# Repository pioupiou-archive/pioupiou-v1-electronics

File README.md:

# pioupiou-v1-electronics

This repository contains the electronic parts of the Pioupiou V1 wind sensor.

## DEPRECATION NOTICE
**THIS REPOSITORY IS NO LONGER ACTIVE.**

**PLEASE MOVE TO THE NEW PROJECT: https://github.com/windbird-sensor/windbird-electronics**

## License

Copyright (c) 2015 Bac Plus Zéro SAS

Copyright (c) 2016 Altostratus SA

Copyright (c) 2021 OpenWindMap SCIC SA and contributors

**Permission is granted to anyone to use this Material for any purpose, including commercial applications, and to alter it and redistribute it freely, subject to the following restrictions:**

**ATTRIBUTION:** You must give appropriate credit, provide a link to the license, and indicate if changes were made. You may do so in any reasonable manner, but not in any way that suggests the licensor endorses you or your use.

**SHARE-ALIKE:** If you remix, transform, or build upon the Material, you must distribute your contributions under the same license as the original. You must include a copy of this License with every copy of this Material or modified version of this Material You distribute or otherwise make available.

**OBLIGATION TO SHARE WITHIN THE OPENWINDMAP NETWORK:** If you use this Material or a modified version of this Material to build a product that collects environmental data, this data must be published within the OpenWindMap network. You must not intentionally degrade the quality of the data, reduce the accuracy of its geolocation or delay its dissemination.

**OPEN-DATA:** If you use this Material or a modified version of this Material to build a product that collects environmental data, this data should be published under an Open-Data license. The chosen license must allow free reuse and redistribution, including from commercial entities and for commercial use. The choosen license must either be compliant with the [Open Definition](https://opendefinition.org/od/2.1/en/) or receive approval from OpenWindMap's board. You are allowed to offer a version of this data under any other license of your choice (including non-free licenses), as long as you also provide an identical version of this data under an Open-Data license as defined in this paragraph.

**DISCLAIMER OF WARRANTY/LIMITATION OF REMEDIES:** OpenWindMap and its contributors have no obligation to support this Material. OpenWindMap and its contributors are providing this Material "AS IS", with no express or implied warranties of any kind, including, but not limited to, any implied warranties of merchantability or fitness for any particular purpose or warranties against infringement of any proprietary rights of a third party.

**OpenWindMap and its contributors will not be liable for any consequential, incidental, or special damages, or any other relief, or for any claim by any third party, arising from your use of this Material.**

For the avoidance of doubt, OpenWindMap may offer this Material under separate terms or conditions or stop distributing this Material at any time; however, doing so will not terminate this License.

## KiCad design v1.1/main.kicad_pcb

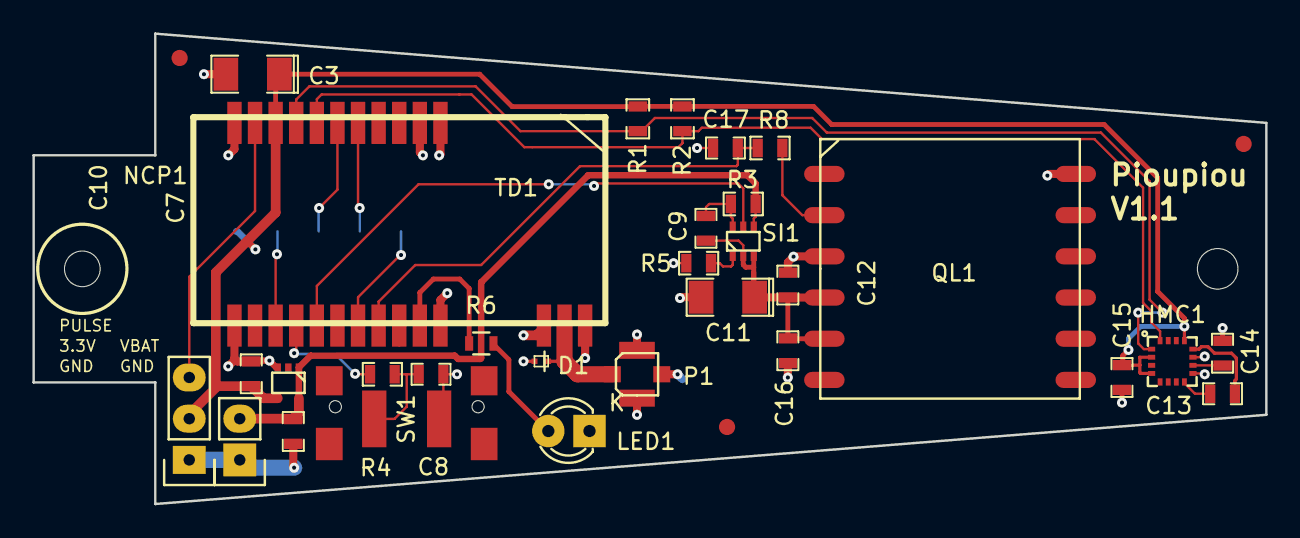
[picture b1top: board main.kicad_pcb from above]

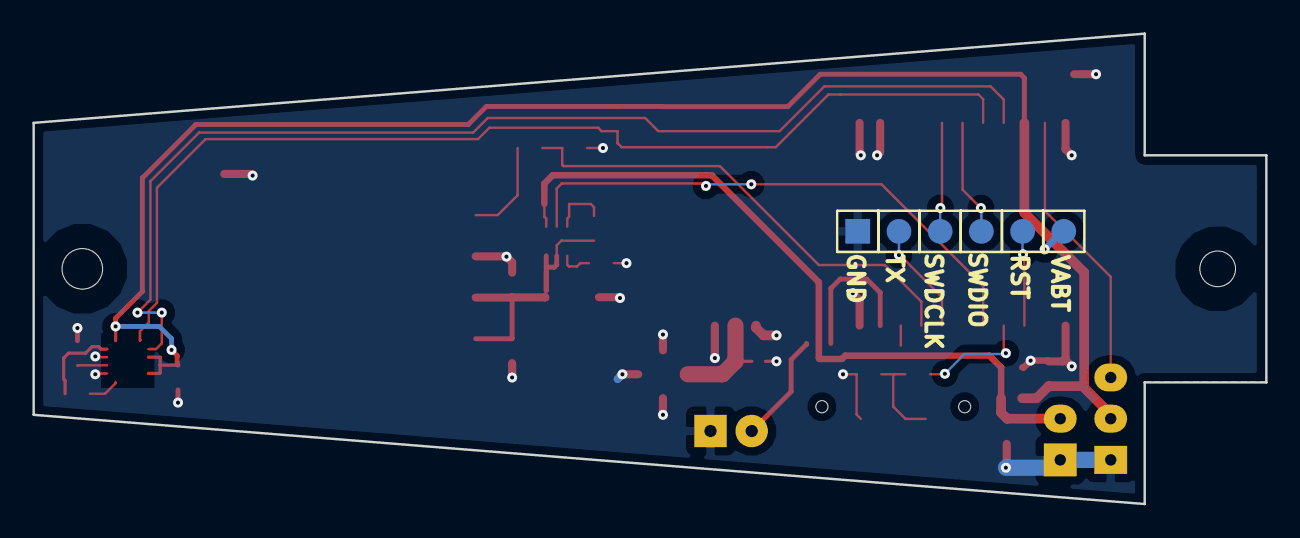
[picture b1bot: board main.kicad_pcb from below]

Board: 2 copper layers, 76.0 x 29.0 mm, 39 parts (6 on the bottom side), 23 nets.

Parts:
BT1: AAA; VIS_BATTERIE
C3: 10uF/6V3; SM1206POL
C7, C10, C12, C16: 100n; SM0603_Capa
C8: 10nF; SM0603_Capa
C9, C17: vide; SM0603_Capa
C11: 10u; SM1206POL
C13: 220nF; SM0603_Capa
C14: 4.7uF; SM0603_Capa
C15: 100nF; SM0603_Capa
D1: ESD9R3.3ST5G; sod923
HMC1: HMC5883L
K1: CONN_3; Socket_Strip_Straight_1x03
LED1: LED-3MM
MIRE-1MM, MIRE-1MM#2, MIRE-1MM#3: VAL**; MIRE-1MM
NCP1: NCP4681
P1: CONN_2; UFL
P3, P4, P5, P6, P7, P8: CONN_1; PIN_ARRAY_1
QL1: L80; PA6H
R1, R2, R4: 10k; SM0603_Resistor
R3: 1M; SM0603_Resistor
R5: 0R; SM0603_Resistor
R6: R_0603
R8: 10K; SM0603_Resistor
SI1: SI1865DL; si1865dl
SW1: SW_PUSH; 1571300
TD1: TD1208

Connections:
/GPSBCKP: C16.1, QL1.5, TD1.17
/GPSVIO: SI1.5, TD1.16
/PULSE_SW: K1.3, TD1.10
/RF: D1.1, P1.1, TD1.24
/RST: P6.1, TD1.14
/RX: C17.1, R8.2, TD1.19
/SCL: HMC1.1, R1.2, TD1.8
/SDA: HMC1.16, R2.2, TD1.7
/SWDCLK: P5.1, TD1.5
/SWDIO: P4.1, TD1.6
/TX: P8.1, TD1.18
/USR_SW: R4.1, TD1.15
/V33: C3.1, C10.1, C15.1, HMC1.2, HMC1.4, HMC1.13, K1.2, NCP1.4, P3.1, R1.1, R2.1, TD1.9
/VBAT: C7.1, NCP1.1, NCP1.5, R3.1, SI1.4
GND: C3.2, C7.2, C8.2, C10.2, C11.2, C12.2, C14.2, C15.2, C16.2, C17.2, D1.2, HMC1.9, HMC1.11, K1.1, LED1.1, NCP1.3, P1.2, P7.1, QL1.3, QL1.12, R5.2, SW1.2, TD1.1, TD1.2, TD1.11, TD1.12, TD1.22, TD1.23, TD1.25
unnamed: R5.1, SI1.1
unnamed: QL1.2, R8.1
unnamed: C9.1, R3.2, SI1.6
unnamed: C9.2, C11.1, C12.1, QL1.4, SI1.2, SI1.3
unnamed: C14.1, HMC1.10
unnamed: C13.1, HMC1.8
unnamed: C13.2, HMC1.12
unnamed: C8.1, R4.2, SW1.1

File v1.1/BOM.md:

| **Designator**        | **Package** | **Quantity** | **Designation**             |
| --------------------- | ----------- | ------------ | --------------------------- |
| C3, C11               | 1206        | 2            | 10uF X7R 6.3V 10%           |
| C13                   | 0603        | 1            | 220nF X7R 6.3V 10%          |
| C14                   | 0603        | 1            | 4.7uF X5R 6.3V 10%          |
| C16,C10,C7,C12,C15,C6 | 0603        | 6            | 100nF X7R 6.3V 10%          |
| C17,C9                | 0603        | 2            | do not populate             |
| C8                    | 0603        | 1            | 10nF X7R 6.3V 10%           |
| D1                    | sod923      | 1            | ESD9R3.3ST5G                |
| LED1                  | Trough-hole | 1            | LTL1CHKEKNN                 |
| NCP1                  | SC70        | 1            | NCP4681DSQ33T1G             |
| P1                    | UFL         | 1            | U.FL-R-SMT-1                |
| R3                    | 0603        | 1            | 1M 1%                       |
| R4,R1,R2              | 0603        | 3            | 10k 1%                      |
| R5                    | 0603        | 1            | 0R                          |
| R6                    | 0603        | 1            | 68 1%                       |
| R8                    | 0603        | 1            | 10K 1%                      |
| SI1                   | SC70-6      | 1            | SI1865DDL-T1-GE3            |
| SW1                   | smd switch  | 1            | 1571300-2 (TE Connectivity) |
| TD1                   | module      | 1            | TD1208R                     |
| TMR1                  | sot23       | 1            | TMR1202 / TMR1208           |
| HMC1                  | lcc 3x3mm   | 1            | HMC5883L                    |
| QL1                   | module      | 1            | L80                         |

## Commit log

2021-03-11 Archive upload
2021-03-11 battery connector
